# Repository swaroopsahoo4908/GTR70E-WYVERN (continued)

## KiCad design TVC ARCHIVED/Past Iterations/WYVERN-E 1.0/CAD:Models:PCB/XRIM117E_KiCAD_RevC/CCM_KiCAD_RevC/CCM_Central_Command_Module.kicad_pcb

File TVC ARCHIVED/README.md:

# TVC ARCHIVED

Everything from the thrust-vector-control revision that the fin-control vehicle does not reuse, moved here on 2026-10-15 with its folder structure intact:

- `Documentation/`: E4 docs, BOMs, FEA, PID reports, presentation deck, `MATH_DERIVATIONS.md` (still holds the ToF-ring math)
- `Flight Computer/`: the Pico 2 W perfboard firmware `wyvern4_tvc`, TVC/solenoid ground rigs, perfboard wiring generators, flowcharts
- `Simulations/`: `we4_*` engines, the `wyvern_datagen` GUI suite, `.ork`, plots; `CFD_outputs_TVC/` keeps the TVC-era polars
- `3D parts/`: E4 airframe, gimbal, MTVC, superseded parts, `gen_rocket4.py`
- `Motor Test Stand/TVC Thrust-Vector Balance/`, `Data/TVC (vector + control)/`
- `Senior Research/`: the TVC proposal (md/docx/pdf)
- `Past Iterations/`: WYVERN-E 1.0 / 3.0, KiCad and EasyEDA PCB history, arc-sim
- `README_TVC.md`, `_All Files.md`

Carried forward (copied or adapted, not moved): the vortex-panel CFD method and section families, `wcad.py`, the Jerrod H tunnel STLs, the static thrust stand, the F15 thrust data, the Pico 2 W (now the ground station), and the firmware's dual-core / seqlock / logging patterns.

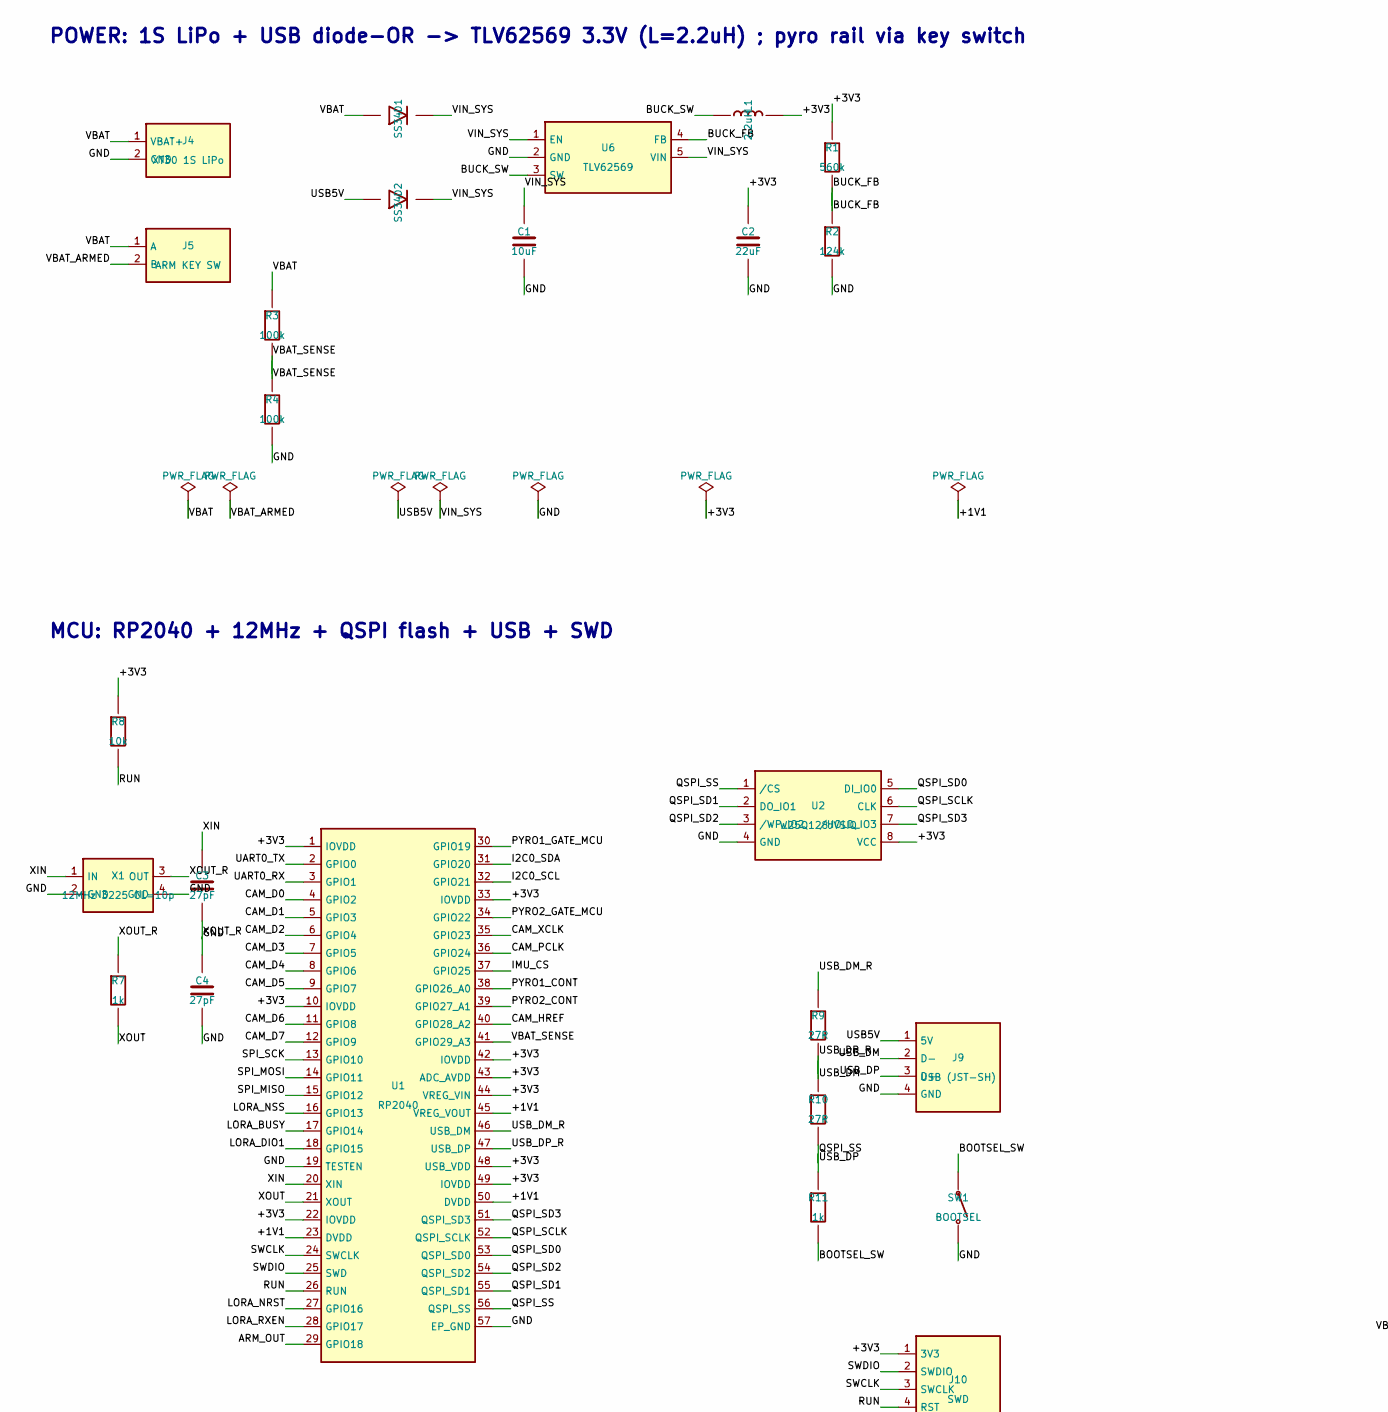
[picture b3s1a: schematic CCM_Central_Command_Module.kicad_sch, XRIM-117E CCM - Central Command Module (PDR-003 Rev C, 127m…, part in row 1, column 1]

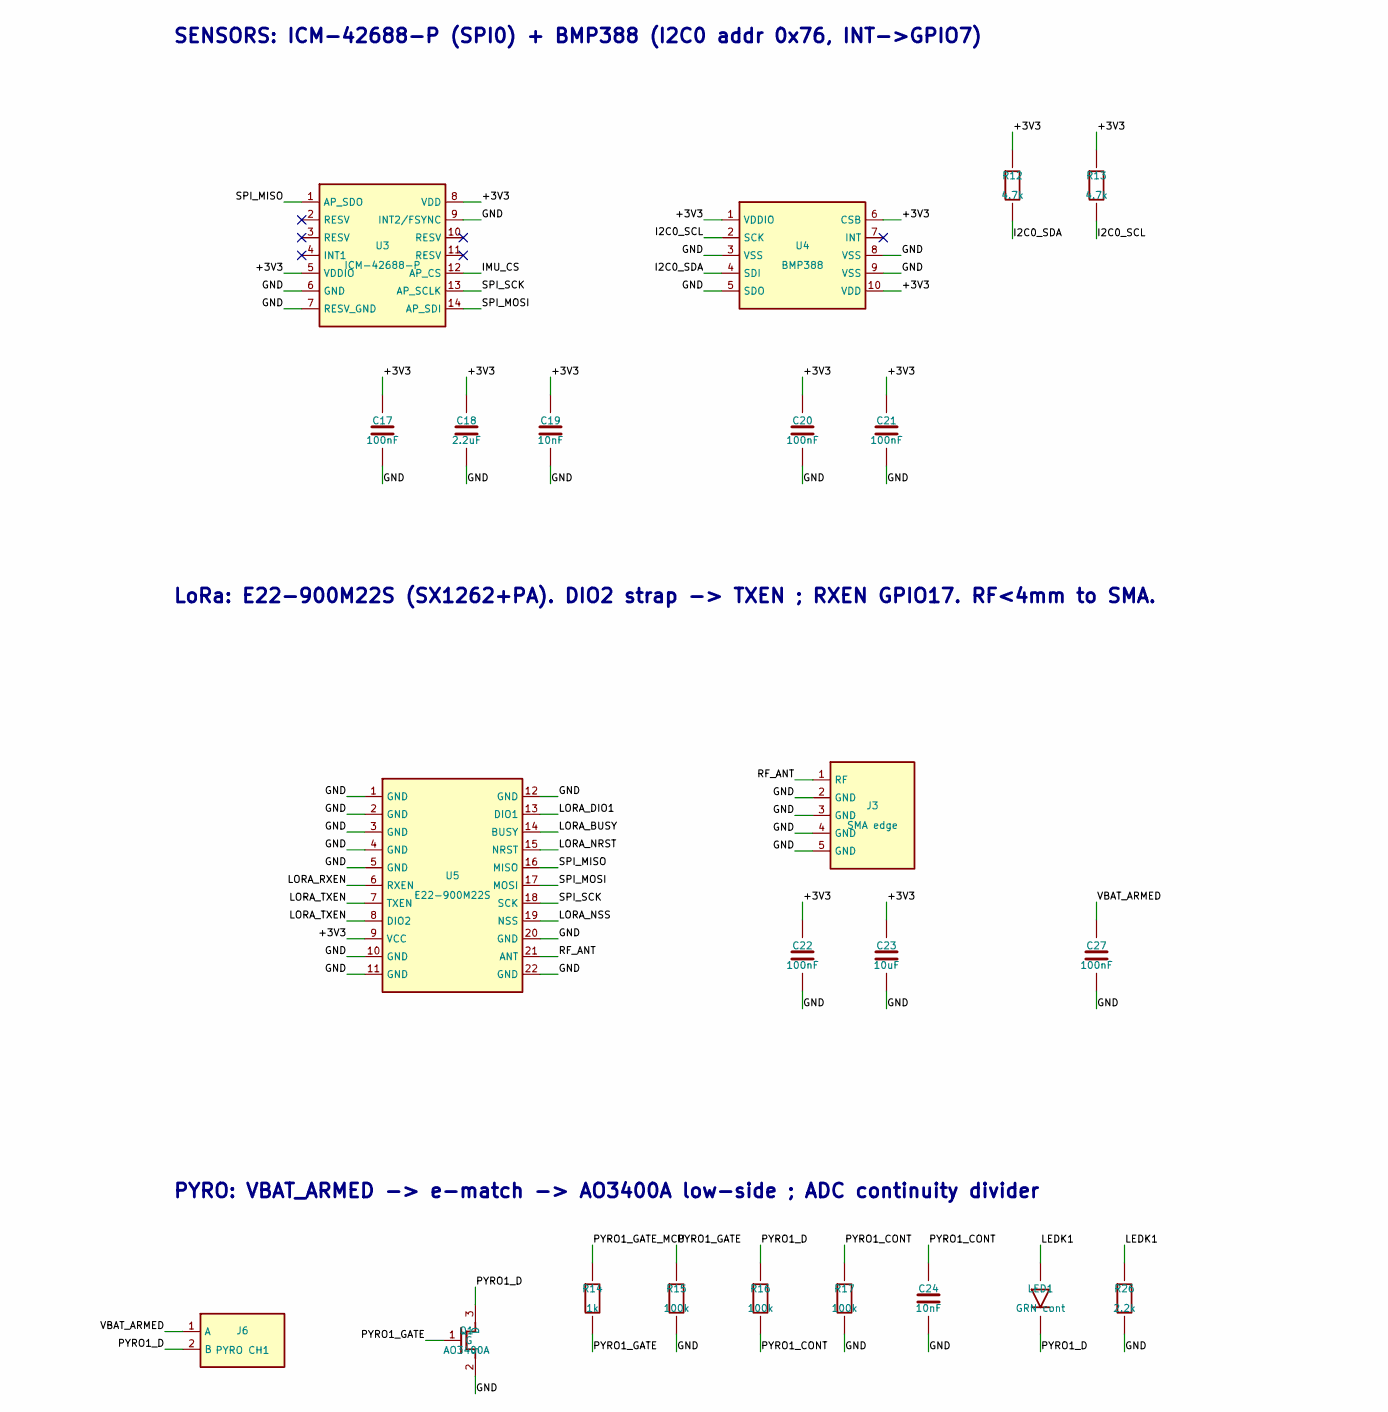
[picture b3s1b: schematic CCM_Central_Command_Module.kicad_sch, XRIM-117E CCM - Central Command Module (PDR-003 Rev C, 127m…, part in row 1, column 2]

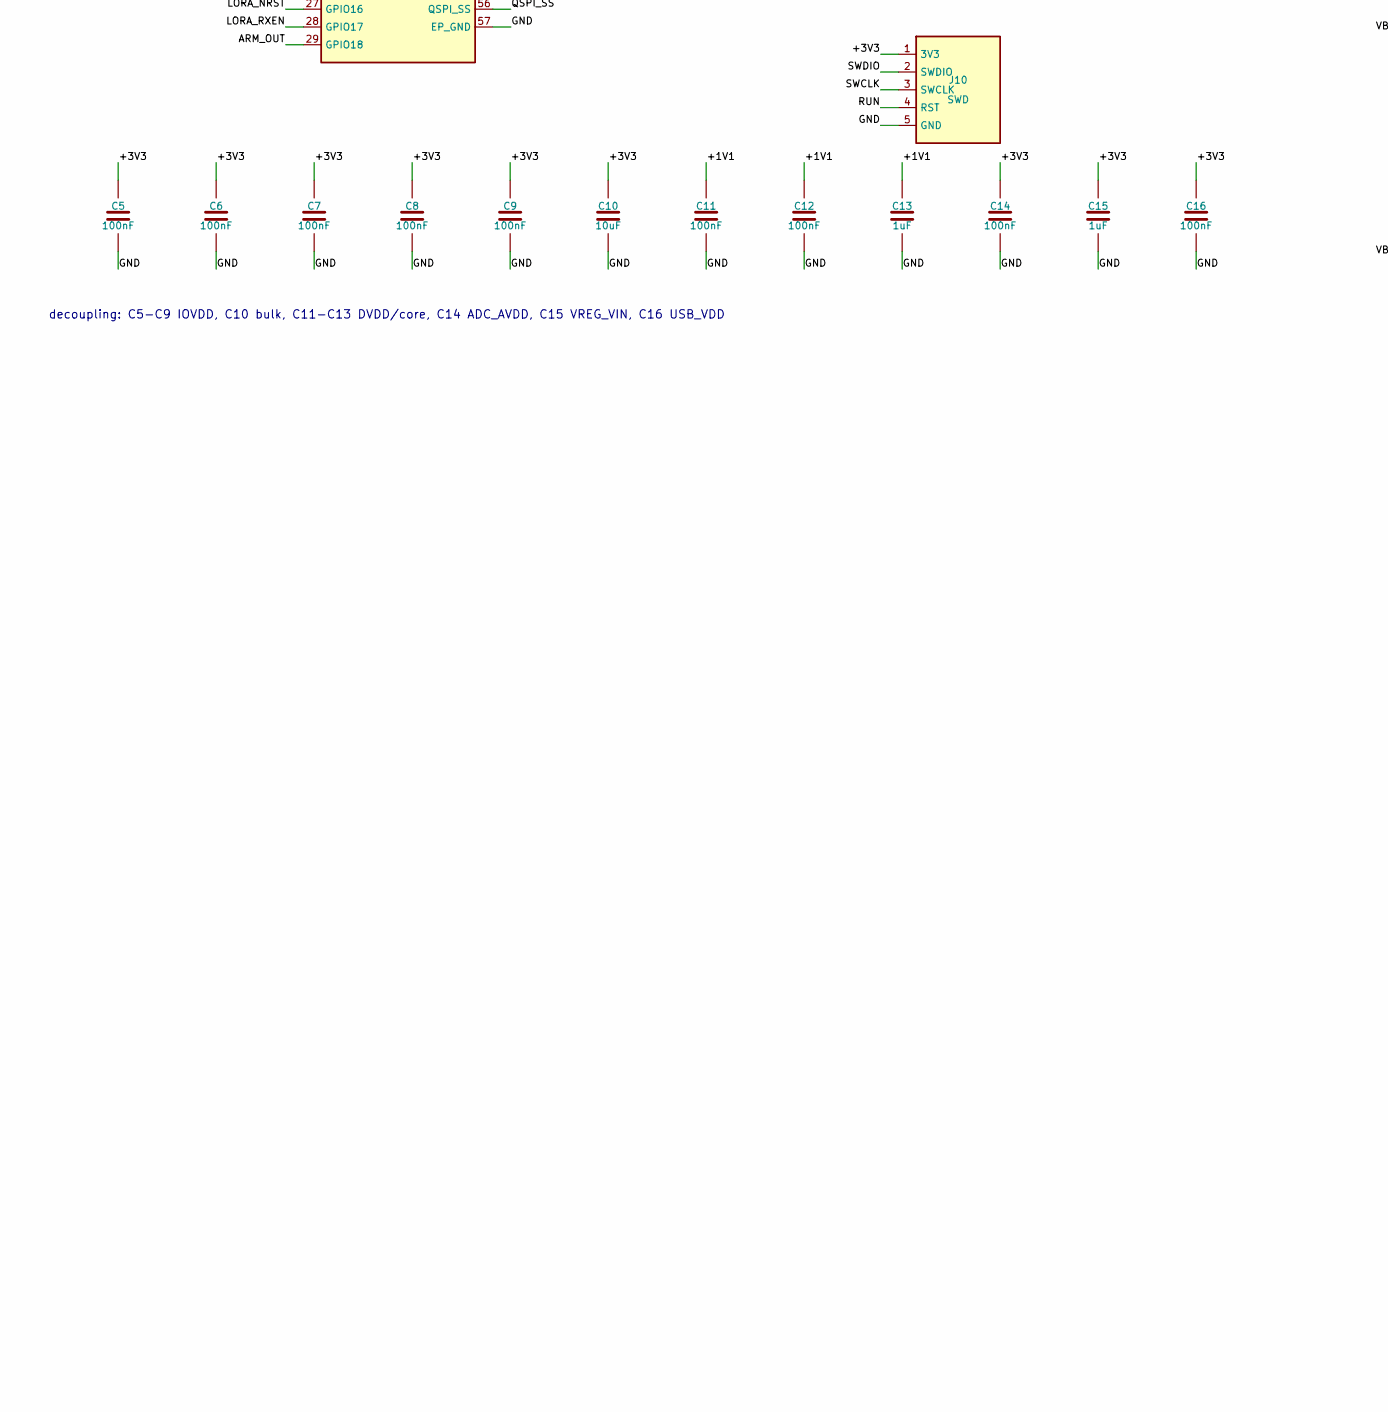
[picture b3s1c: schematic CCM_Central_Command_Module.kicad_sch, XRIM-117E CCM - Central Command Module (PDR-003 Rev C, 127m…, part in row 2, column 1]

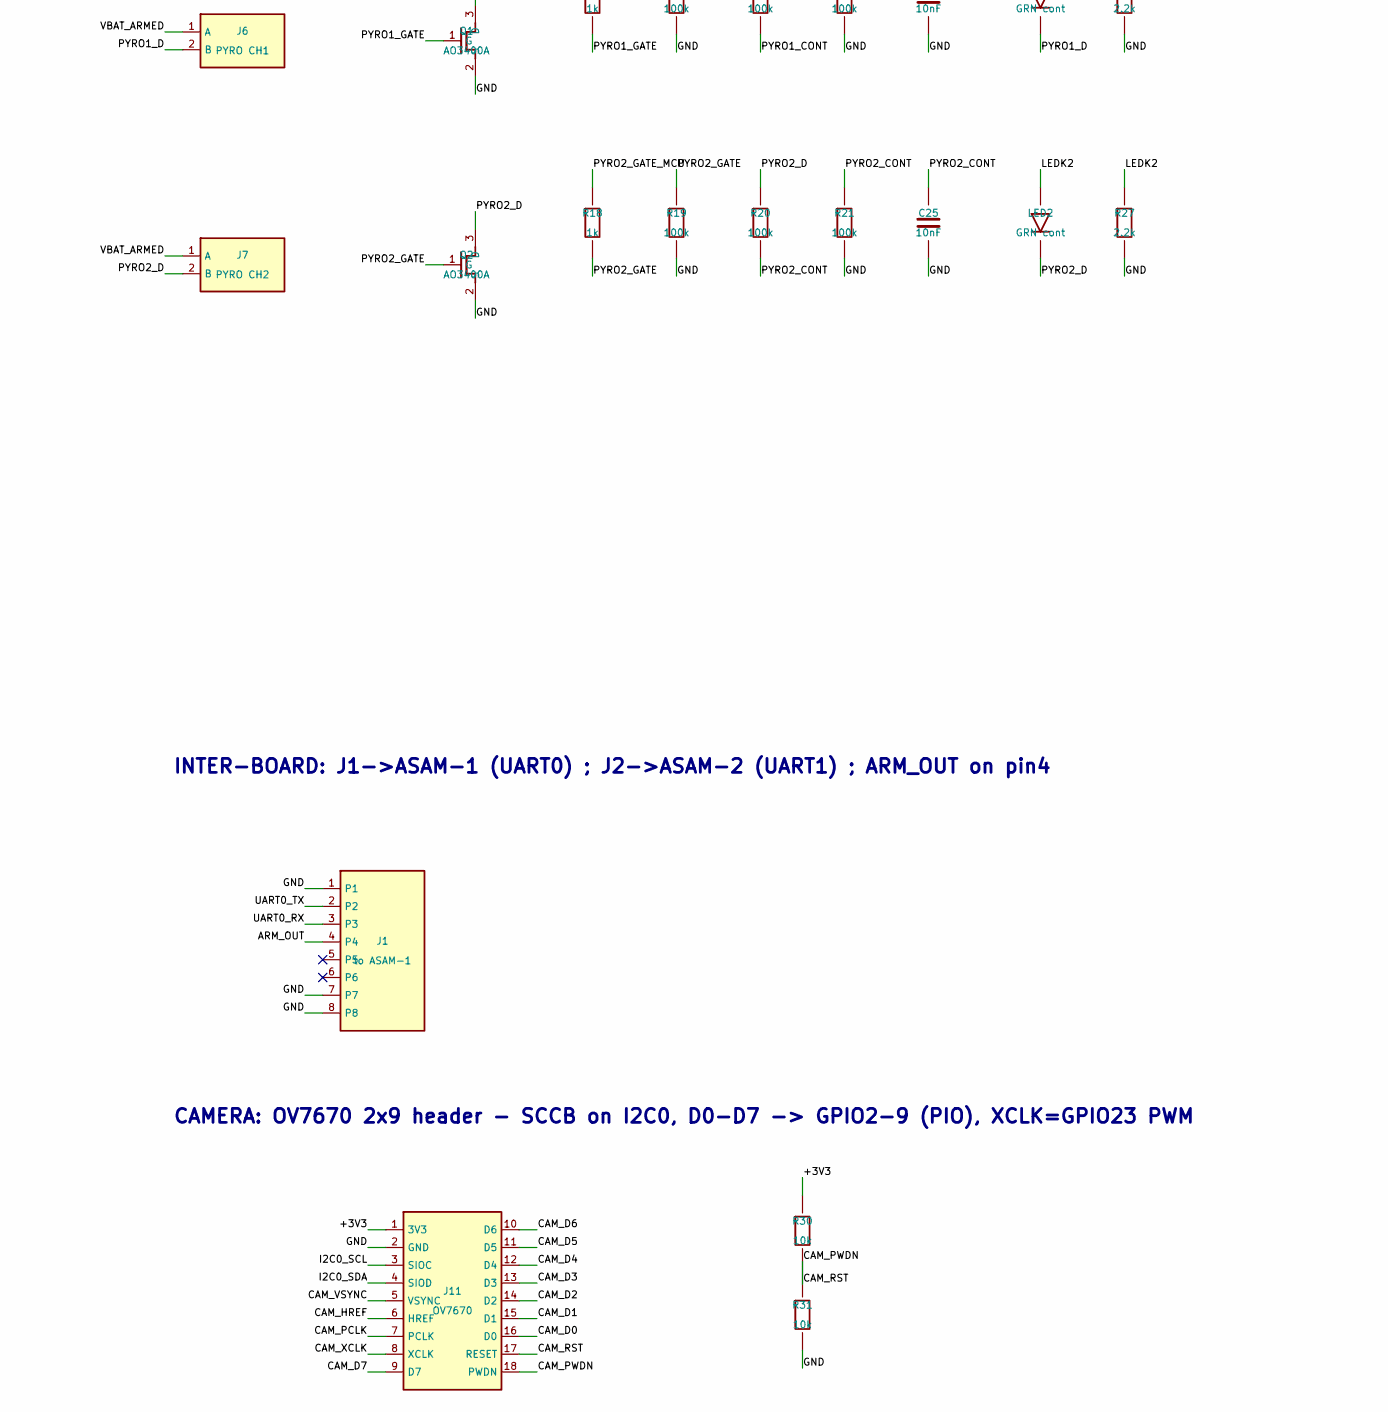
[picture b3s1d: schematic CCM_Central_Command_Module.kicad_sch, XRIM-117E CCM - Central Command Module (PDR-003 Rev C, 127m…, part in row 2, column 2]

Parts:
C1, C10, C23: 10uF
C2: 22uF
C3, C4: 27pF
C5, C6, C7, C8, C9, C11, C12, C14, C16, C17, C20, C21, C22, C27: 100nF
C13, C15: 1uF
C18: 2.2uF
C19, C24, C25: 10nF
D1, D2: SS34; D_SMA
J1: to ASAM-1
J3: SMA edge
J4: XT30 1S LiPo
J5: ARM KEY SW
J6: PYRO CH1
J7: PYRO CH2
J9: USB (JST-SH)
J10: SWD
J11: OV7670
L1: 2.2uH; L_4x4mm
LED1, LED2: GRN cont
Q1, Q2: AO3400A
R1: 560k
R2: 124k
R3, R4, R15, R16, R17, R19, R20, R21: 100k
R7, R11, R14, R18: 1k
R8, R30, R31: 10k
R9, R10: 27R
R12, R13: 4.7k
R26, R27: 2.2k
SW1: BOOTSEL
U1: RP2040
U2: W25Q128JVSIQ
U3: ICM-42688-P
U4: BMP388
U5: E22-900M22S
U6: TLV62569
X1: 12MHz 3225 CL=10p

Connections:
+1V1: C11.1, C12.1, C13.1, U1.23 (DVDD), U1.45 (VREG_VOUT), U1.50 (DVDD)
+3V3: C2.1, C5.1, C6.1, C7.1, C8.1, C9.1, C10.1, C14.1, C15.1, C16.1, C17.1, C18.1, C19.1, C20.1, C21.1, C22.1, C23.1, J10.1 (3V3), J11.1 (3V3), L1.2, R1.1, R8.1, R12.1, R13.1, R30.1, U1.1 (IOVDD), U1.10 (IOVDD), U1.22 (IOVDD), U1.33 (IOVDD), U1.42 (IOVDD), U1.43 (ADC_AVDD), U1.44 (VREG_VIN), U1.48 (USB_VDD), U1.49 (IOVDD), U2.8 (VCC), U3.5 (VDDIO), U3.8 (VDD), U4.1 (VDDIO), U4.6 (CSB), U4.10 (VDD), U5.9 (VCC)
ARM_OUT: J1.4, U1.29 (GPIO18)
BOOTSEL_SW: R11.2, SW1.1
BUCK_FB: R1.2, R2.1, U6.4 (FB)
BUCK_SW: L1.1, U6.3 (SW)
CAM_D0: J11.16 (D0), U1.4 (GPIO2)
CAM_D1: J11.15 (D1), U1.5 (GPIO3)
CAM_D2: J11.14 (D2), U1.6 (GPIO4)
CAM_D3: J11.13 (D3), U1.7 (GPIO5)
CAM_D4: J11.12 (D4), U1.8 (GPIO6)
CAM_D5: J11.11 (D5), U1.9 (GPIO7)
CAM_D6: J11.10 (D6), U1.11 (GPIO8)
CAM_D7: J11.9 (D7), U1.12 (GPIO9)
CAM_HREF: J11.6 (HREF), U1.40 (GPIO28_A2)
CAM_PCLK: J11.7 (PCLK), U1.36 (GPIO24)
CAM_PWDN: J11.18 (PWDN), R31.1
CAM_RST: J11.17 (RESET), R30.2
CAM_VSYNC: J11.5 (VSYNC)
CAM_XCLK: J11.8 (XCLK), U1.35 (GPIO23)
I2C0_SCL: J11.3 (SIOC), R13.2, U1.32 (GPIO21), U4.2 (SCK)
I2C0_SDA: J11.4 (SIOD), R12.2, U1.31 (GPIO20), U4.4 (SDI)
IMU_CS: U1.37 (GPIO25), U3.12 (AP_CS)
LEDK1: LED1.1, R26.1
LEDK2: LED2.1, R27.1
LORA_BUSY: U1.17 (GPIO14), U5.14 (BUSY)
LORA_DIO1: U1.18 (GPIO15), U5.13 (DIO1)
LORA_NRST: U1.27 (GPIO16), U5.15 (NRST)
LORA_NSS: U1.16 (GPIO13), U5.19 (NSS)
LORA_RXEN: U1.28 (GPIO17), U5.6 (RXEN)
LORA_TXEN: U5.7 (TXEN), U5.8 (DIO2)
PYRO1_CONT: C24.1, R16.2, R17.1, U1.38 (GPIO26_A0)
PYRO1_D: J6.2 (B), LED1.2, Q1.3 (D), R16.1
PYRO1_GATE: Q1.1 (G), R14.2, R15.1
PYRO1_GATE_MCU: R14.1, U1.30 (GPIO19)
PYRO2_CONT: C25.1, R20.2, R21.1, U1.39 (GPIO27_A1)
PYRO2_D: J7.2 (B), LED2.2, Q2.3 (D), R20.1
PYRO2_GATE: Q2.1 (G), R18.2, R19.1
PYRO2_GATE_MCU: R18.1, U1.34 (GPIO22)
QSPI_SCLK: U1.52 (QSPI_SCLK), U2.6 (CLK)
QSPI_SD0: U1.53 (QSPI_SD0), U2.5 (DI_IO0)
QSPI_SD1: U1.55 (QSPI_SD1), U2.2 (DO_IO1)
QSPI_SD2: U1.54 (QSPI_SD2), U2.3 (/WP_IO2)
QSPI_SD3: U1.51 (QSPI_SD3), U2.7 (/HOLD_IO3)
RF_ANT: J3.1 (RF), U5.21 (ANT)
RUN: J10.4 (RST), R8.2, U1.26 (RUN)
SPI_MISO: U1.15 (GPIO12), U3.1 (AP_SDO), U5.16 (MISO)
SPI_MOSI: U1.14 (GPIO11), U3.14 (AP_SDI), U5.17 (MOSI)
SPI_SCK: U1.13 (GPIO10), U3.13 (AP_SCLK), U5.18 (SCK)
SWCLK: J10.3 (SWCLK), U1.24 (SWCLK)
SWDIO: J10.2 (SWDIO), U1.25 (SWD)
UART0_RX: J1.3, U1.3 (GPIO1)
UART0_TX: J1.2, U1.2 (GPIO0)
USB5V: D2.1, J9.1 (5V)
USB_DM: J9.2 (D-), R9.2
USB_DM_R: R9.1, U1.46 (USB_DM)
USB_DP_R: R10.1, U1.47 (USB_DP)
VBAT: D1.1, J4.1 (VBAT+), J5.1 (A), R3.1
VBAT_ARMED: C27.1, J5.2 (B), J6.1 (A), J7.1 (A)
VBAT_SENSE: R3.2, R4.1, U1.41 (GPIO29_A3)
VIN_SYS: C1.1, D1.2, D2.2, U6.1 (EN), U6.5 (VIN)
XIN: C3.1, U1.20 (XIN), X1.1 (IN)
XOUT: R7.2, U1.21 (XOUT)

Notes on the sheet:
POWER: 1S LiPo + USB diode-OR -> TLV62569 3.3V (L=2.2uH) ; pyro rail via key switch
MCU: RP2040 + 12MHz + QSPI flash + USB + SWD
decoupling: C5-C9 IOVDD, C10 bulk, C11-C13 DVDD/core, C14 ADC_AVDD, C15 VREG_VIN, C16 USB_VDD
SENSORS: ICM-42688-P (SPI0) + BMP388 (I2C0 addr 0x76, INT->GPIO7)
LoRa: E22-900M22S (SX1262+PA). DIO2 strap -> TXEN ; RXEN GPIO17. RF<4mm to SMA.
PYRO: VBAT_ARMED -> e-match -> AO3400A low-side ; ADC continuity divider
INTER-BOARD: J1->ASAM-1 (UART0) ; J2->ASAM-2 (UART1) ; ARM_OUT on pin4
CAMERA: OV7670 2x9 header - SCCB on I2C0, D0-D7 -> GPIO2-9 (PIO), XCLK=GPIO23 PWM

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
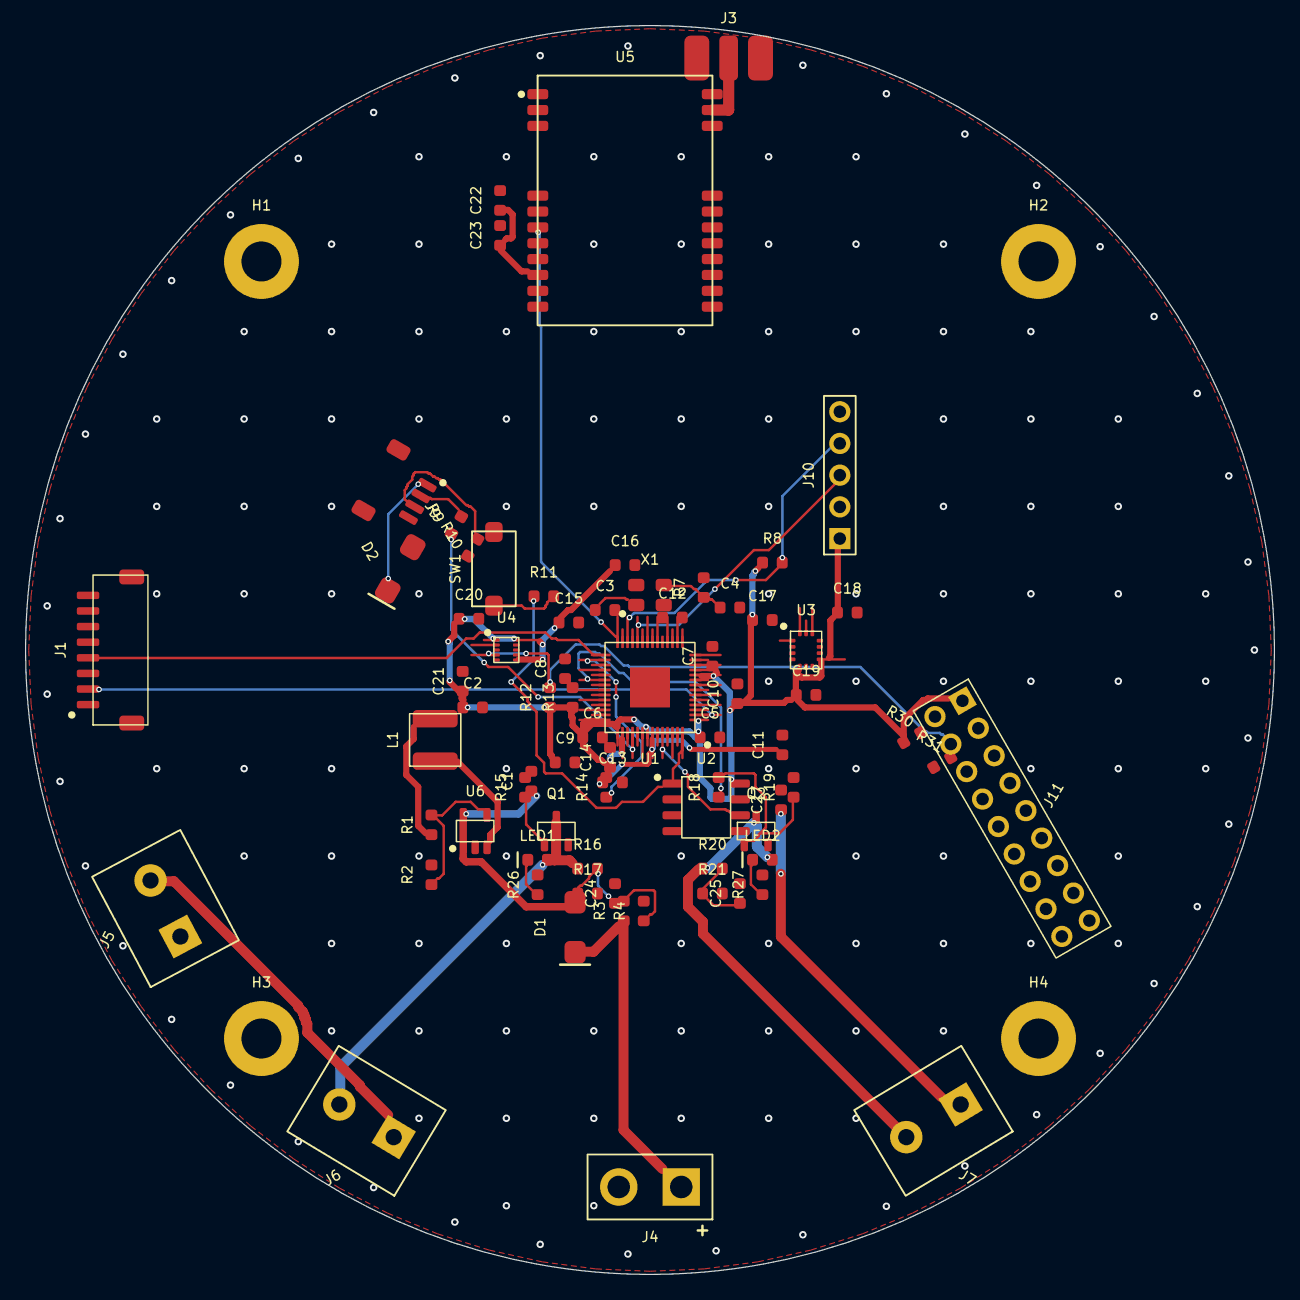
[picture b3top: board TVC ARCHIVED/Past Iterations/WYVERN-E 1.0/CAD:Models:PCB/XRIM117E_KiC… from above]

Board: 2 copper layers, 100.0 x 100.0 mm, 77 parts (0 on the bottom side), 66 nets.

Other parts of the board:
H1, H2, H3, H4: M3; MountingHole_M3

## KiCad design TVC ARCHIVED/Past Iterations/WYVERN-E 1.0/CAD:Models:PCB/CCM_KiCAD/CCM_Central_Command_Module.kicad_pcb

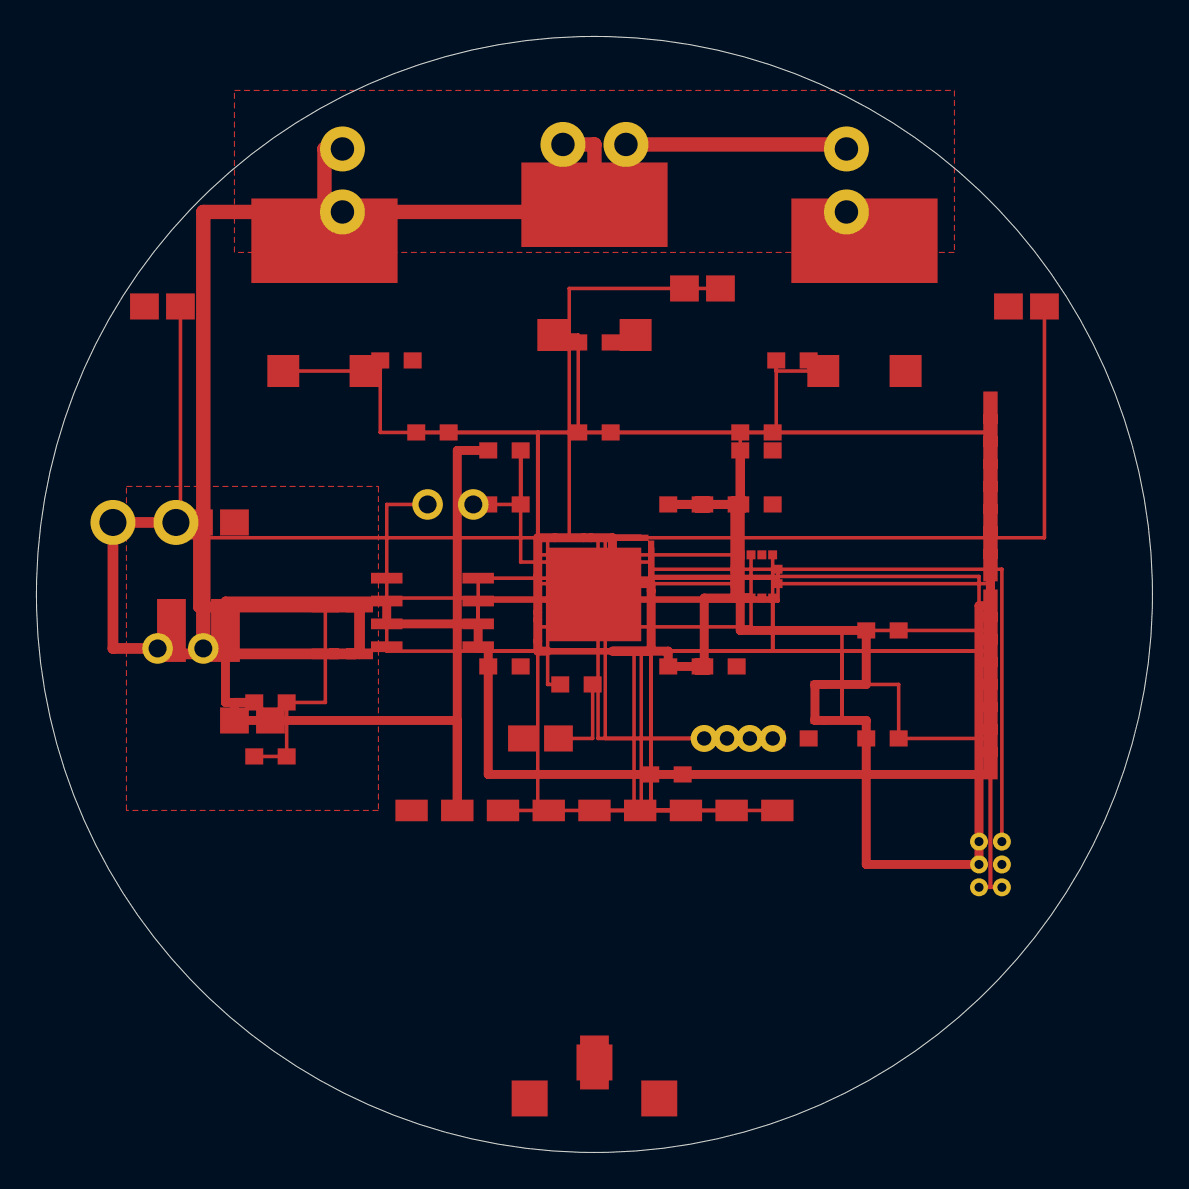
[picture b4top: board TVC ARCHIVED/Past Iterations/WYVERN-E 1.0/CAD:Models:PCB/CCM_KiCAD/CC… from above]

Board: 2 copper layers, 62.0 x 62.0 mm, 49 parts (0 on the bottom side), 45 nets.

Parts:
C1: 47uF 10V; C_0805_2012Metric
C2: 22uF 6.3V; C_0805_2012Metric
C10, C12, C13, C14, C15, C20, C21, C30, C31: 100nF; C_0402_1005Metric
C11: 10uF; C_0402_1005Metric
J1, J2: JST-GH-8; JST_GH_SM08B-GHS-TB_1x08-1MP_P1.25mm_Horizontal
J3: SMA_Edge; SMA_Molex_0732511150_Horizontal
J4: XT30-M; PinHeader_1x02_P2.54mm_Vertical
J5: SW_2pin; PinHeader_1x02_P2.54mm_Vertical
J6, J7, J8: Screw_2; TerminalBlock_bornier-2_P3.5mm
J9: USB_TP; PinHeader_1x04_P1.27mm_Vertical
L1: 2.2uH; L_1210_3225Metric
LED1, LED2, LED3: Cont LED; LED_0805_2012Metric
LED4: Status; LED_0805_2012Metric
Q1, Q2, Q3: IRFZ44N; TO-263-3_TabEP
R1, R23, R24, R25: 10k; R_0402_1005Metric
R10, R11: 4.7k; R_0402_1005Metric
R20, R21, R22: 100R; R_0402_1005Metric
R26: 453k; R_0402_1005Metric
R27: 100k; R_0402_1005Metric
R28: 330R; R_0402_1005Metric
SW1: TC2030-SWD; TC2030-IDC-FP_2x03_P1.27mm_Vertical
SW_BOOT: SW_2pin; PinHeader_1x02_P2.54mm_Vertical
U1: RP2040; QFN-56-1EP_7x7mm_P0.4mm
U2: W25Q128; SOIC-8_3.9x4.9mm_P1.27mm
U3: ICM-42688-P; InvenSense_ICM-42688-P_LGA-14
U4: BMP388; Bosch_LGA-8_2x2.5mm
U5: E22-900M22S; Ebyte_E22-900M22S
U6: TLV62569; SOT-23-5

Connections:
+3V3: C2.1, C10.1, C11.1, C13.1, C14.1, C15.1, C20.1, C21.1, C30.1, J1.1, J2.1, L1.2, R1.1, R10.1, R11.1, R26.1, SW1.3, U1.1, U1.10, U1.22, U1.23, U1.33, U1.36, U1.37, U1.41, U1.47, U1.52, U1.53, U1.56, U2.3, U2.7, U2.8, U3.1, U3.2, U3.12, U4.1, U4.2, U4.7, U5.8
BUCK_SW: L1.1, U6.1
FB_3V3: R26.2, R27.1, U6.5
FLASH_CS: SW_BOOT.1, U1.8, U2.1
GND: C1.2, C2.2, C10.2, C11.2, C12.2, C13.2, C14.2, C15.2, C20.2, C21.2, C30.2, C31.2, J1.2, J2.2, J3.2, J3.3, J4.2, J9.1, LED1.K, LED2.K, LED3.K, LED4.K, Q1.2, Q2.2, Q3.2, R23.2, R24.2, R25.2, R27.2, SW1.4, SW_BOOT.2, U1.9, U1.19, U1.20, U1.21, U1.27, U1.28, U1.29, U1.30, U1.31, U1.32, U1.43, U1.49, U1.50, U1.55, U1.EP, U2.4, U3.3, U3.8, U3.11, U4.3, U4.6, U4.8, U5.9, U6.2
I2C0_SCL: J1.6, J2.6, R11.2, U1.12, U4.4
I2C0_SDA: J1.5, J2.5, R10.2, U1.11, U4.5
IMU_CS: U1.7, U3.7
IMU_INT1: U1.54, U3.9
IMU_INT2: U1.48, U3.10
LED_MCU: R28.1, U1.42
LED_STATUS: LED4.A, R28.2
LORA_BUSY: U1.17, U5.5
LORA_CS: U1.16, U5.4
LORA_IRQ: U1.18, U5.6
LORA_MISO: U1.15, U5.3
LORA_MOSI: U1.14, U5.2
LORA_NRST: U1.51, U5.7
LORA_SCK: U1.13, U5.1
NRST: C12.1, R1.2, U1.26
PYRO1_CONT: LED1.A, U1.40
PYRO1_D: J6.2, Q1.EP
PYRO1_GATE: J1.8, Q1.1, R20.2, R23.1
PYRO1_MCU: R20.1, U1.46
PYRO2_CONT: LED2.A, U1.39
PYRO2_D: J7.2, Q2.EP
PYRO2_GATE: J2.8, Q2.1, R21.2, R24.1
PYRO2_MCU: R21.1, U1.45
PYRO3_CONT: LED3.A, U1.38
PYRO3_D: J8.2, Q3.EP
PYRO3_GATE: Q3.1, R22.2, R25.1
PYRO3_MCU: R22.1, U1.44
RF_ANT: J3.1, U5.10
SPI0_MISO: U1.6, U2.2, U3.4
SPI0_MOSI: U1.5, U2.5, U3.6
SPI0_SCK: J1.7, J2.7, U1.4, U2.6, U3.5
SWCLK: SW1.1, U1.24
SWDIO: SW1.2, U1.25
UART0_RX: J1.4, J2.4, SW1.6, U1.3
UART0_TX: J1.3, J2.3, SW1.5, U1.2
USB5V: C31.1, J9.4
USB_DM: J9.2, U1.34
USB_DP: J9.3, U1.35
VBAT: C1.1, J4.1, J5.1, U6.3, U6.4
VBAT_ARMED: J5.2, J6.1, J7.1, J8.1

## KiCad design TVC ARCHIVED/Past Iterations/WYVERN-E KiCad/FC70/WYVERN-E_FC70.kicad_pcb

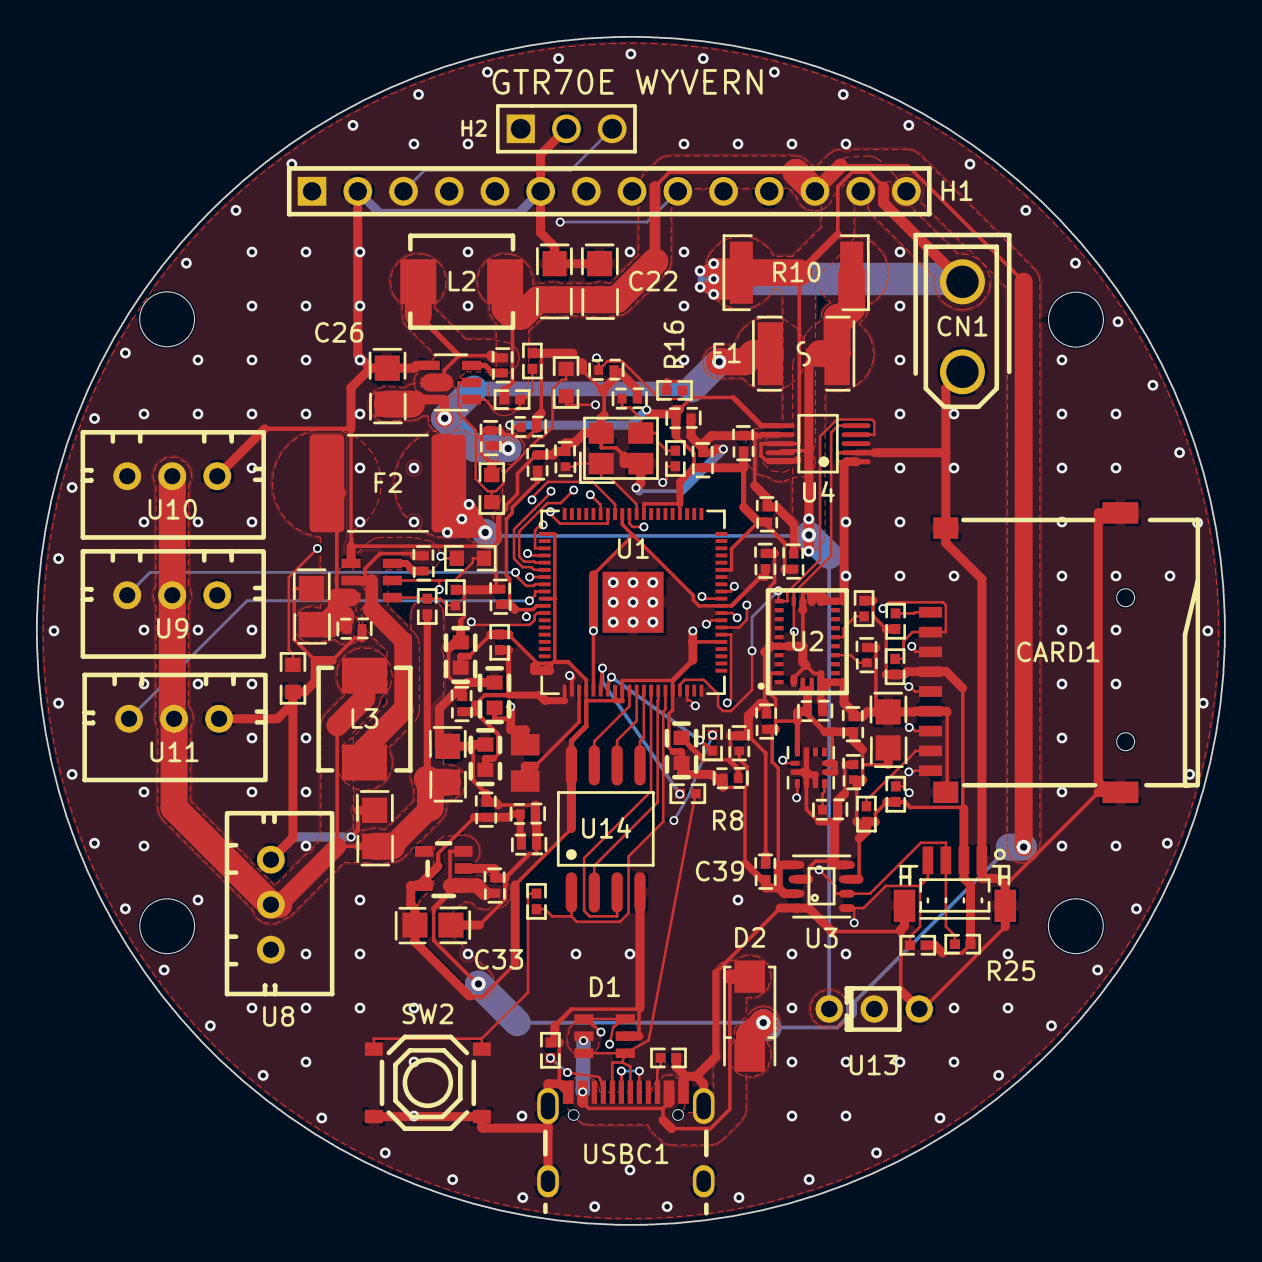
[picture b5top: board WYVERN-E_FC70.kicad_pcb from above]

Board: 4 copper layers, 66.0 x 66.0 mm, 99 parts (0 on the bottom side), 61 nets.

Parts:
C1, C2: 15pF; C0402
C3, C4, C5, C34: 4.7uF; C0603
C6, C7, C8, C9, C10, C11, C12, C13, C14, C15, C16, C17, C18, C19, C20, C23, C24, C25, C27, C28, C30, C36, C37, C38, C39, C40, C41: 100nF; C0402
C21: 22uF; C0805_v2
C22, C31, C32: 22uF; C0805
C26, C29: 10uF 25V; C0805
C33, C35: 10uF; C0805
C42: 1uF; C0402
CARD1: TF-01A; TF-SMD_TF-01A
CN1: XT30UPB-M; CONN-TH_XT30UPB-M
CN2: BM04B-SRSS-TB; CONN-SMD_BM04B-SRSS-TB
D1: USBLC6-2SC6; SOT-23-6_L2.9-W1.6-P0.95-LS2.8-BL
D2: SS14; SMA_L4.4-W2.6-LS5.0-RD
F1: 2.6A PTC; F1812
F2: 3A PTC; Fuse_2920_7451Metric
H1: 1x14 2.54; HDR-TH_14P-P2.54-V-M_4
H2: SWD 1x3; HDR-TH_3P-P2.54-V-M-1
L1: 3.3uH; IND-SMD_L2.0-W1.6_AOTA-B201610S3R3-101-T
L2, L3: 3.3uH; IND-SMD_L5.7-W5.1
MH1, MH2, MH3, MH4: MountingHole
R1, R11: 1k; R0402
R2: 33; R0402
R5, R22: 56k; R0402
R6, R9, R16, R18, R19, R20, R21, R23: 10k; R0402
R7, R8: 27; R0402
R10: 10mΩ 2W; R2512
R12, R13: 5.1k; R0402
R14, R24: 100k; R0603
R15, R17: 33k; R0603
R25, R26: 4.7k; R0402
SW2: BOOTSEL; SW-SMD_4P-L5.1-W5.1-P3.70-LS6.5-TL_H1.5
U1: RP2350B; QFN-80_L10.0-W10.0-P0.40-TL-EP3.4
U2: BNO055; LGA-28_L5.2-W3.8-P0.50-BL
U3: BME680; LGA-8_L3.0-W3.0-P0.80-TR
U4: INA226; MSOP-10_L3.0-W3.0-P0.50-LS5.0-BL
U5: LIS3MDL; LGA-12_L2.0-W2.0-P0.50-BL
U6: TPS564201; SOT-23-6_L2.9-W1.6-P0.95-LS2.8-BL
U7: AP2112K-3.3; SOT-23-5_L2.9-W1.6-P0.95-LS2.8-BR
U8, U9, U10, U11: B3B-XH-A; CONN-TH_3P-P2.50_A2501WV2-3P
U12: 12MHz; CRYSTAL-SMD_4P-L3.2-W2.5-BL
U13: SS-12D00-G3; SW-TH_3P-L8.8-W3.9-P2.50_SS12D00G3
U14: W25Q128JVSIQ; SOIC-8_L5.3-W5.3-P1.27-LS8.0-BL
U15: TPS564201; SOT-23-6_L2.9-W1.6-P0.95-LS2.8-BL_v2
USBC1: TYPE-C-31-M-12; USB-C_SMD-TYPE-C-31-M-12_1

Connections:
+1V1_DVDD: C17.1, C19.1, C20.1, C34.1, L1.2, U1.10, U1.32, U1.51, U1.65
+3V3: C4.1, C5.1, C8.1, C9.1, C10.1, C11.1, C12.1, C13.1, C14.1, C15.1, C16.1, C18.1, C23.1, C24.1, C33.1, C35.1, C36.1, C37.1, C38.1, C39.1, CARD1.4, CN2.2, H1.1, H1.5, R2.2, R9.2, R16.1, R18.1, R19.1, R20.1, R21.1, R25.2, R26.2, U1.5, U1.15, U1.24, U1.29, U1.41, U1.50, U1.59, U1.60, U1.64, U1.68, U1.69, U1.76, U2.3, U2.4, U2.28, U3.2, U3.6, U3.8, U4.6, U5.5, U5.6, U5.10, U7.5, U14.8
+5V: C21.1, C22.1, C42.1, D2.1, H1.12, L2.2, R5.1, U7.1, U7.3
BOOTSEL_R: R11.2, SW2.1, SW2.2
BUCK5_BST: C6.1, U15.6
BUCK5_EN: R14.2, R15.1, U15.5
BUCK5_FB: R5.2, R6.1, U15.4
BUCK5_SW: C6.2, L2.1, U15.2
BUCK5_VIN: C26.1, C40.1, F1.1, U15.3
BUCKSV_BST: C30.1, U6.6
BUCKSV_EN: R17.2, R24.2, U6.5
BUCKSV_FB: R22.2, R23.1, U6.4
BUCKSV_SW: C30.2, L3.1, U6.2
BUCKSV_VIN: C29.1, C41.1, F2.1, U6.3
GND: C1.2, C2.2, C3.2, C4.2, C5.2, C7.2, C8.2, C9.2, C10.2, C11.2, C12.2, C13.2, C14.2, C15.2, C16.2, C17.2, C18.2, C19.2, C20.2, C21.2, C22.2, C23.2, C24.2, C25.2, C26.2, C27.2, C28.2, C29.2, C31.2, C32.2, C33.2, C34.2, C35.2, C36.2, C37.2, C38.2, C39.2, C40.2, C41.2, C42.2, CARD1.6, CARD1.10, CARD1.11, CARD1.12, CARD1.13, CN1.1, CN2.0, CN2.1, D1.2, H1.2, H1.6, H1.11, H1.14, H2.2, R6.2, R12.2, R13.2, R15.2, R17.1, R23.2, SW2.3, SW2.4, U1.62, U1.81, U2.2, U2.5, U2.6, U2.15, U2.16, U2.17, U2.18, U2.25, U3.1, U3.5, U3.7, U4.1, U4.2, U4.7, U5.2, U5.3, U5.9, U5.12, U6.1, U7.2, U8.3, U9.3, U10.3, U11.3, U12.2, U12.4, U13.3, U14.4, U15.1, USBC1.1, USBC1.2, USBC1.3, USBC1.4, USBC1.A1B12, USBC1.B1A12
HDR_GPIO12: H1.13, U1.11
HDR_GPIO34: H1.10, U1.43
HDR_GPIO35: H1.9, U1.44
HDR_GPIO36: H1.8, U1.45
HDR_GPIO37: H1.7, U1.46
I2C_SCL: CN2.4, R26.1, U1.78, U2.19, U3.4, U4.5, U5.1
I2C_SDA: CN2.3, R25.1, U1.77, U2.20, U3.3, U4.4, U5.11
IMU_CAP: C27.1, U2.9
IMU_NRST: R9.1, U2.11
MAG_C1: C25.1, U5.4
PWR_EN: R14.1, R24.1, U13.2
QSPI_SCLK: U1.71, U14.6
QSPI_SD0: U1.72, U14.5
QSPI_SD1: U1.74, U14.2
QSPI_SD2: U1.73, U14.3
QSPI_SD3: U1.70, U14.7
QSPI_SS: R11.1, U1.75, U14.1
RUN: C28.1, R16.2, U1.35
SD_CD: CARD1.9, U1.12
SD_CLK: CARD1.5, U1.8
SD_CMD_MOSI: CARD1.3, U1.9
SD_CS: CARD1.2, R21.2, U1.7
SD_DAT0_MISO: CARD1.7, R18.2, U1.6
SD_DAT1: CARD1.8, R19.2
SD_DAT2: CARD1.1, R20.2
SERVO1_PWM: U1.52, U8.1
SERVO2_PWM: U1.48, U9.1
SERVO3_PWM: U1.47, U10.1
SERVO4_PWM: U1.49, U11.1
SWCLK: H1.4, H2.1, U1.33
SWDIO: H1.3, H2.3, U1.34
USBC_DN: D1.1, D1.6, R8.2, USBC1.A7, USBC1.B7
USBC_DP: D1.3, D1.4, R7.2, USBC1.A6, USBC1.B6
USB_CC1: R12.1, USBC1.A5
USB_CC2: R13.1, USBC1.B5
USB_DN: R8.1, U1.66
USB_DP: R7.1, U1.67
VBAT: CN1.2, R10.1, U4.8, U4.10
VBAT_SHUNT: F1.2, F2.2, R10.2, U4.9, U13.1
VBUS: D1.5, D2.2, USBC1.A4B9, USBC1.B4A9
VREG_AVDD: C3.1, C7.1, R2.1, U1.61
VREG_LX: L1.1, U1.63
VSERVO: C31.1, C32.1, L3.2, R22.1, U8.2, U9.2, U10.2, U11.2
XIN: C1.1, U1.30, U12.1
XOUT: R1.1, U1.31
XOUT_R: C2.1, R1.2, U12.3

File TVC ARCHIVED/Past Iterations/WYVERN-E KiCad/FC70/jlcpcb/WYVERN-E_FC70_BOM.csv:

Comment,Designator,Footprint,LCSC Part #,Manufacturer Part,Quantity
15pF,"C1,C2",C0402,C1548,0402CG150J500NT,2
4.7uF,"C3,C4,C5,C34",C0603,C19666,CL10A475KO8NNNC,4
100nF,"C6,C7,C8,C9,C10,C11,C12,C13,C14,C15,C16,C17,C18,C19,C20,C23,C24,C25,C27,C28,C30,C36,C37,C38,C39,C40,C41",C0402,C1525,CL05B104KO5NNNC,27
22uF,C21,C0805_v2,C45783,CL21A226MAQNNNE,1
22uF,"C22,C31,C32",C0805,C45783,CL21A226MAQNNNE,3
10uF 25V,"C26,C29,C33,C35",C0805,C15850,CL21A106KAYNNNE,4
1uF,C42,C0402,C52923,CL05A105KA5NQNC,1
TF-01A,CARD1,TF-SMD_TF-01A,C91145,TF-01A,1
XT30UPB-M,CN1,CONN-TH_XT30UPB-M,C428721,XT30UPB-M,1
BM04B-SRSS-TB,CN2,CONN-SMD_BM04B-SRSS-TB,C160390,BM04B-SRSS-TB(LF)(SN),1
USBLC6-2SC6,D1,SOT-23-6_L2.9-W1.6-P0.95-LS2.8-BL,C7519,USBLC6-2SC6,1
SS14,D2,SMA_L4.4-W2.6-LS5.0-RD,C112424,SS14,1
2.6A PTC,F1,F1812,C438899,SMD1812P260TF/16,1
3A PTC,F2,Fuse_2920_7451Metric,C20829,SMD2920P300TF/15,1
1x14 2.54,H1,HDR-TH_14P-P2.54-V-M_4,C49569637,2011-1X14G00SB,1
SWD 1x3,H2,HDR-TH_3P-P2.54-V-M-1,C49257,2.54-1*3PPin,1
3.3uH,L1,IND-SMD_L2.0-W1.6_AOTA-B201610S3R3-101-T,C42411119,AOTA-B201610S3R3-101-T,1
3.3uH,"L2,L3",IND-SMD_L5.7-W5.1,C3002618,CKST0503-3.3uH/M,2
1k,"R1,R11",R0402,C11702,0402WGF1001TCE,2
33,R2,R0402,C25105,0402WGF330JTCE,1
56k,"R5,R22",R0402,C25796,0402WGF5602TCE,2
10k,"R6,R9,R16,R18,R19,R20,R21,R23",R0402,C25744,0402WGF1002TCE,8
27,"R7,R8",R0402,C25100,0402WGF270JTCE,2
10mΩ 2W,R10,R2512,C192580,RLM25FEER010,1
5.1k,"R12,R13",R0402,C25905,0402WGF5101TCE,2
100k,"R14,R24",R0603,C25803,0603WAF1003T5E,2
33k,"R15,R17",R0603,C25779,0402WGF3302TCE,2
4.7k,"R25,R26",R0402,C25900,0402WGF4701TCE,2
BOOTSEL,SW2,SW-SMD_4P-L5.1-W5.1-P3.70-LS6.5-TL_H1.5,C318884,TS-1187A-B-A-B,1
RP2350B,U1,QFN-80_L10.0-W10.0-P0.40-TL-EP3.4,C42415655,RP2350B,1
BNO055,U2,LGA-28_L5.2-W3.8-P0.50-BL,C93216,BNO055,1
BME680,U3,LGA-8_L3.0-W3.0-P0.80-TR,C125972,BME680,1
INA226,U4,MSOP-10_L3.0-W3.0-P0.50-LS5.0-BL,C49851,INA226AIDGSR,1
LIS3MDL,U5,LGA-12_L2.0-W2.0-P0.50-BL,C478483,LIS3MDLTR,1
TPS564201,U6,SOT-23-6_L2.9-W1.6-P0.95-LS2.8-BL,C464812,TPS564201DDCR,1
AP2112K-3.3,U7,SOT-23-5_L2.9-W1.6-P0.95-LS2.8-BR,C23380830,AP2112K-3.3TRG1,1
B3B-XH-A,"U8,U9,U10,U11",CONN-TH_3P-P2.50_A2501WV2-3P,C144394,B3B-XH-A(LF)(SN),4
12MHz,U12,CRYSTAL-SMD_4P-L3.2-W2.5-BL,C20625731,ABM8-272-T3,1
SS-12D00-G3,U13,SW-TH_3P-L8.8-W3.9-P2.50_SS12D00G3,C22355741,SS-12D00-G3,1
W25Q128JVSIQ,U14,SOIC-8_L5.3-W5.3-P1.27-LS8.0-BL,C97521,W25Q128JVSIQ,1
TPS564201,U15,SOT-23-6_L2.9-W1.6-P0.95-LS2.8-BL_v2,C464812,TPS564201DDCR,1
TYPE-C-31-M-12,USBC1,USB-C_SMD-TYPE-C-31-M-12_1,C165948,TYPE-C-31-M-12,1
